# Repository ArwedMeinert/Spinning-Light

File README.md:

# Spinning Light

___  
This project combines dynamic RGB lighting with a home trainer to enhance your workout experience. The lamp pairs with a power trainer, mapping your power output to its LEDs. The displayed color corresponds to different zones based on your set FTP value. During sprints, the LEDs flash red and yellow to motivate you in your "pain cave."  

All parameters—such as LED brightness, FTP value, and the power trainer’s Bluetooth address—can be adjusted via the GUI. Under **Advanced Settings**, you can modify the zone percentages, LED filter constants, and the number of pixels.  
___  
On the main screen, sensor data for humidity and temperature is displayed. The second page shows the current power output, while the third page displays the Bluetooth address and the power trainer's name.
___
Check out the Youtube Video about the project:

---

# Microcontroller and Code

The lamp is built around an ESP32 NodeMCU Mini to keep the design compact. The firmware was developed using the Arduino IDE with the ESP32 board definitions (select Node32s). The encoder’s built-in push button is handled without an interrupt, which improves performance and reduces false button detections. A physical pull-up resistor is used, so the internal pull-up is disabled on that pin.

## Connecting Bluetooth

Bluetooth Low Energy (BTLE) is used for connectivity, with the necessary library included in the sketch. Ideally, the device writes the trainer’s address to the EEPROM for automatic reconnection on subsequent startups. However, while the ESP can reconnect automatically after a trainer is initially connected, it does not do so after a restart and must search for the trainer again. Once connected, the ESP subscribes to the power service of the trainer and receives its power data, which is then mapped to LED colors.

---

# Casing

The casing is designed for modularity. Openings for the display, encoder, temperature sensor, and USB port can be finalized after printing. This also allows you to hardcode the Bluetooth address if you prefer not to use the GUI.

---

# PCB

The PCB is designed to work with DuPont connectors for all external components. The ESP is mounted on the back to leave space for the casing lid. The ESP's USB-C port is positioned to allow external access if the plastic cover is removed. The board can be powered either via USB or through the 5V connector located in the left opening. The encoder is mounted directly on the PCB and uses three pull-up resistors—two for rotation detection and one for the push button.

Not all supports need to be screwed in; they primarily help stabilize the push button and prevent the PCB from bending under pressure.

---

# Assembly

The temperature sensor is secured to the left side of the casing. To ensure a proper fit, a section of the lid must be removed to allow the sensor's PCB to protrude. The sensor is mounted using M2 screws, fastened from the outside with a nut on the opposite side. This step should be completed first.

Next, insert the screws into the standoff holes. Use at least four screws to secure the PCB; the remaining standoffs primarily support the encoder’s push button. Once the PCB is fixed within the casing, connect the 5V supply if necessary—or use the USB port for power.

Prepare the lid by removing the sections designated for I/O components (the square for the screen and the circle for the encoder). The OLED screen should be equipped with a DuPont connector and then screwed in place. It doesn't matter whether the screen is mounted on the lid or underneath it; however, if it is mounted below, ensure it is properly supported to avoid damage.

Finally, attach the LED profile to the top, ensuring that the cable is routed into the casing. Depending on the LEDs used, prepare the cables according to the PCB's silkscreen guidelines. Once the lid is modified and the connectors are attached, carefully install the lid to avoid interfering with the sensor and encoder. Finally, secure the lid with screws, and your setup should be operational.

## Bill Of Material (BoM)

<details>
  <summary>Click to expand</summary>

| #  | Reference         | Qty | Value                 | Footprint                                                         | DNP |
|----|------------------|-----|----------------------|-----------------------------------------------------------------|-----|
| 1  | J0               | 1   | Power                | Connector_PinHeader_2.54mm:PinHeader_1x02_P2.54mm_Vertical      |     |
| 2  | J1               | 1   | Neopixel             | Connector_PinHeader_2.54mm:PinHeader_1x03_P2.54mm_Horizontal    |     |
| 3  | J2               | 1   | Temperature Sensor   | Connector_PinHeader_2.54mm:PinHeader_1x03_P2.54mm_Horizontal    |     |
| 4  | J3               | 1   | OLED                 | Connector_PinHeader_2.54mm:PinHeader_1x04_P2.54mm_Horizontal    |     |
| 5  | J4               | 1   | Reset                | Connector_PinHeader_2.54mm:PinHeader_1x02_P2.54mm_Vertical      |     |
| 6  | J5               | 1   | Reserve IO23 5VCC    | Connector_PinHeader_2.54mm:PinHeader_1x03_P2.54mm_Horizontal    |     |
| 7  | J6               | 1   | Reserve IO25 5VCC    | Connector_PinHeader_2.54mm:PinHeader_1x03_P2.54mm_Horizontal    |     |
| 8  | J7               | 1   | Reserve IO09 3V3     | Connector_PinHeader_2.54mm:PinHeader_1x03_P2.54mm_Horizontal    |     |
| 9  | J8               | 1   | Reserve IO12 3V3     | Connector_PinHeader_2.54mm:PinHeader_1x03_P2.54mm_Horizontal    |     |
| 10 | J9               | 1   | GND                  | Connector_PinHeader_2.54mm:PinHeader_1x03_P2.54mm_Horizontal    |     |
| 11 | J10              | 1   | 3V3                  | Connector_PinHeader_2.54mm:PinHeader_1x03_P2.54mm_Horizontal    |     |
| 12 | J11              | 1   | 5VCC                 | Connector_PinHeader_2.54mm:PinHeader_1x03_P2.54mm_Horizontal    |     |
| 13 | R1, R2, R3       | 3   | 10k                  | Resistor_THT:R_Axial_DIN0207_L6.3mm_D2.5mm_P7.62mm_Horizontal   |     |
| 14 | SW1              | 1   | RotaryEncoder_Switch | Rotary_Encoder:RotaryEncoder_Alps_EC11E-Switch_Vertical_H20mm   |     |
| 15 | U1               | 1   | esp32-wemos-d1-mini  | ESP32Mini:esp32-wemos-d1-mini                                   |     |
| 16 | U2               | 1   | I2C IIC BiDirektional 5V~3.3V   | Level Shifter:4xLevel Shifter                        |     |
| 17 | WS2812 Neopixel  | 1   | WS2812B LED Strip    | LED Strip (1m)                                                 |     |
| 18 | Diffusion Profile| 1   | Aluminium (1m)       | LED Diffuser Aluminum Profile                                  |     |
| 19 | DHT2302 Sensor   | 1   | DHT2302              | Temperature & Humidity Sensor                                  |     |
| 20 | OLED Display     | 1   | 0.96\" I2C OLED       | 128x64 OLED Display Module                                    |     |

</details>

### Notes:
- The profile is optional, since the controller can be used with any setup of Neopixel. When used as a standalone lamp, 1m is ideal. The amount of LEDs on the strip are also not set (standart value is 144, but it can be changed under advanced settings)
- **DHT2302**: Temperature and humidity sensor (Optional).
- **OLED display**: 0.96\" I2C screen (128x64 resolution).

---

# Usage

Upon startup, the LEDs display random colors. Pressing the encoder takes you to the menu, where you can adjust the FTP, connect the power trainer, and change the brightness (default is 50%). As you adjust the brightness, a preview gradient is shown—from the Z1 color on the first LED to the Z6 color on the last LED.

Within the menu, pressing the back button returns you to the main screen, which displays the current temperature and humidity, power output, or connected device (selectable via the encoder). A symbol in the top right corner indicates whether the power trainer is connected.

Pressing the button again returns you to the main menu. The final option in the menu is the **Advanced Settings** tab. Here, you can adjust the zone percentages (for example, changing the Z1 zone from 60% of FTP to 70% of FTP), the number of LEDs (default is 144), and the filter constants. The filter provides a gradual transition between LED colors using a low-pass algorithm. The filter constant determines the weight of the most recent power reading; for example, a constant of 0.05 means the new color is calculated as 95% of the previous color and 5% of the new value. Since the LEDs refresh multiple times per second, this results in a smooth color transition.

Similarly, the spark constant controls the number of sparks triggered when exceeding zone Z7. A higher spark constant produces more sparks during sprints, while a lower constant produces fewer sparks. The final option in the Advanced Settings tab resets the configuration data to its default values. Once you change a setting and return to the main screen, the settings are saved to the EEPROM and loaded at each startup—so you only need to configure your FTP, trainer address, brightness, and other settings once.

---

# Limitations and Improvements

- **Bluetooth Channels:**  
  ~~The lamp only works with trainers that support at least two Bluetooth channels.~~ It is only possible to connect the lamp and Zwift via bluetooth if the power trainer supports two bluetooth cahannels. It is however possible to connect Zwift via ANT+ and the lamp via BTLE (virtual shifting does not work in this case). I have tested the bluetooth connection with the Wahoo KickrCore and the Zwift Hub. Since the Wahoo KickrCore works, I suspect it will also work with other Wahoo power trainers, although I have not tested them. I welcome any additional information on this topic. See the table below.

- **Automatic Connection Issue:**  
  For some reason, upon startup the microcontroller does not automatically connect to the power trainer, even though the saved address appears to be correct. Manual connection works without issue, and the device reconnects if the power trainer loses power. Despite saving the address in the configuration data, automatic reconnection does not function as expected. I have tried scanning and multiple connection attempts at startup without success. The current workaround is to avoid powering off the lamp (as it consumes minimal power). Any advice on resolving this issue would be greatly appreciated.

- **UI Responsiveness:**  
  At times, the user interface may feel somewhat sluggish, particularly when the encoder is turned rapidly. I suspect this is primarily due to the inexpensive encoder, though other factors may contribute. Turning the encoder slowly generally results in smooth operation.

---

# Known Compatible Power Trainers with Two BT Channels

| Works           | Does Not Work     |
|-----------------|-------------------|
| Wahoo KickrCore | Zwift Hub/Hub One |

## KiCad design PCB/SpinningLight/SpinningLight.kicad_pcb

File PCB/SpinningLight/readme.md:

# PCB 
The PCB makes the wirering easier and allows for easy attatchment of additional sensors. The PCB was created using KiCAD 7.0 and this path includes all files to order and modify the files at hand. 

## Additional Modifications
The PCB already has lanes to multiple GPIO pins of the ESP, allowing easy modification and expansion with more sensor. Some inputs use the additional unused channels of the Level shifter.

___

___

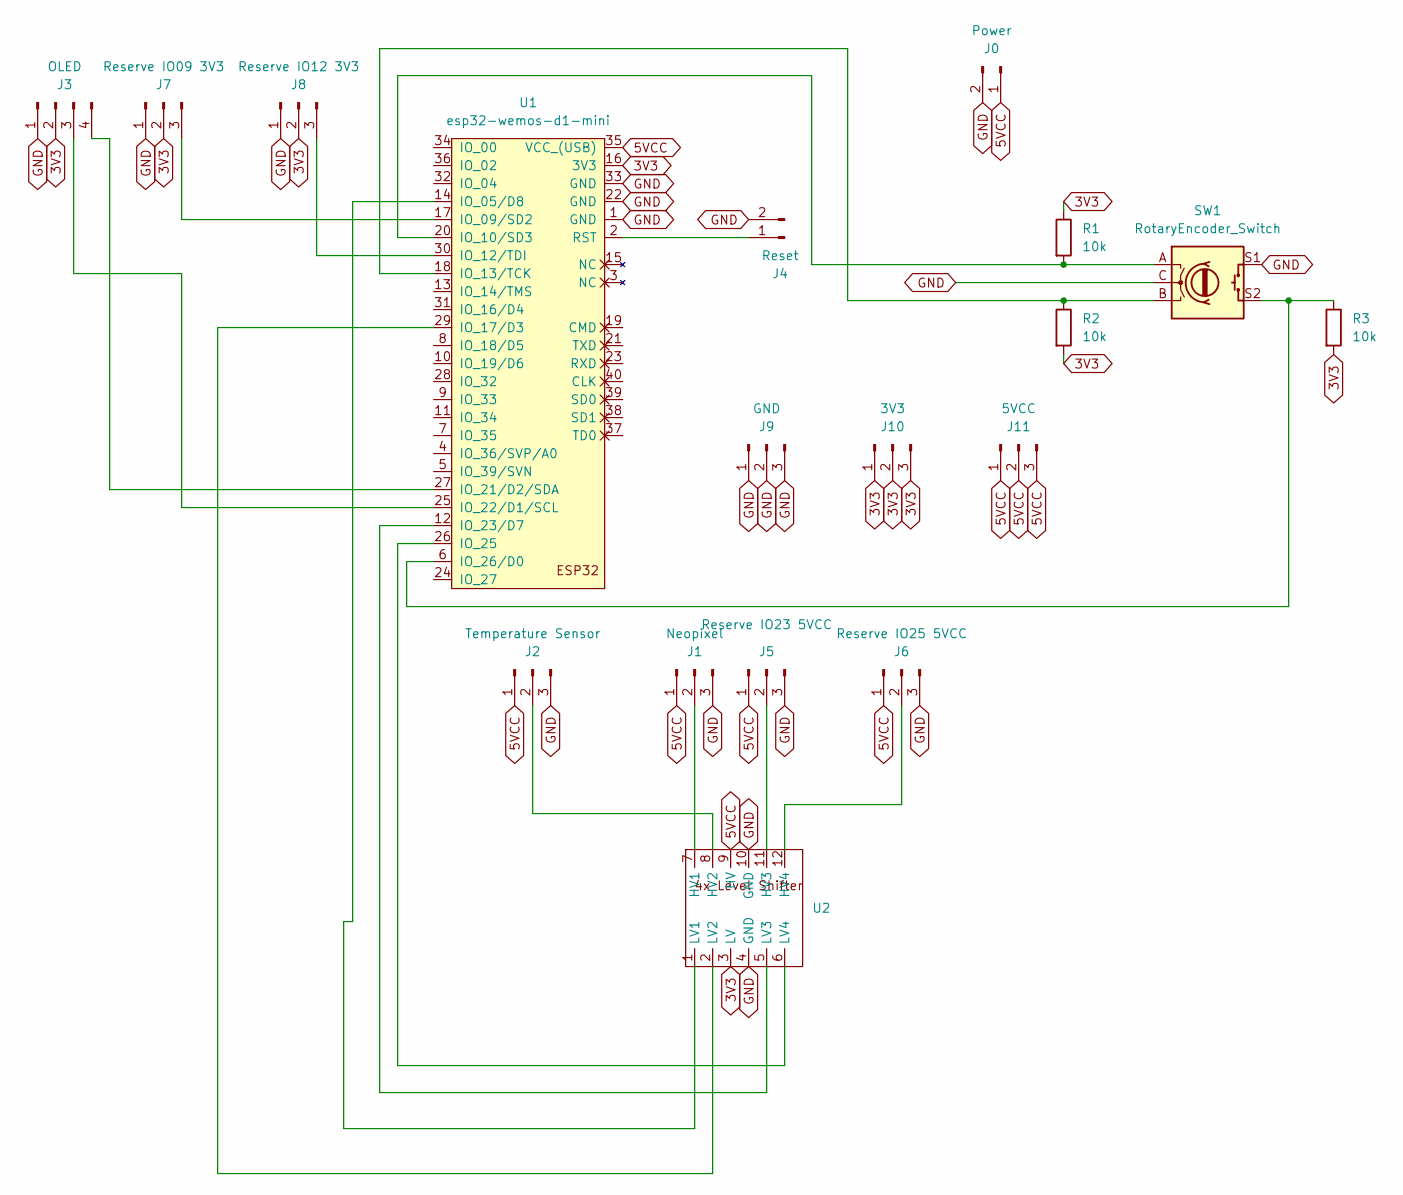
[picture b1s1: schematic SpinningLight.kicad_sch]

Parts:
J0: Power; PinHeader_1x02_P2.54mm_Vertical
J1: Neopixel; PinHeader_1x03_P2.54mm_Horizontal
J2: Temperature Sensor; PinHeader_1x03_P2.54mm_Horizontal
J3: OLED; PinHeader_1x04_P2.54mm_Horizontal
J4: Reset; PinHeader_1x02_P2.54mm_Vertical
J5: Reserve IO23 5VCC; PinHeader_1x03_P2.54mm_Horizontal
J6: Reserve IO25 5VCC; PinHeader_1x03_P2.54mm_Horizontal
J7: Reserve IO09 3V3; PinHeader_1x03_P2.54mm_Horizontal
J8: Reserve IO12 3V3; PinHeader_1x03_P2.54mm_Horizontal
J9: GND; PinHeader_1x03_P2.54mm_Horizontal
J10: 3V3; PinHeader_1x03_P2.54mm_Horizontal
J11: 5VCC; PinHeader_1x03_P2.54mm_Horizontal
R1, R2, R3: 10k; R_Axial_DIN0207_L6.3mm_D2.5mm_P7.62mm_Horizontal
SW1: RotaryEncoder_Switch; RotaryEncoder_Alps_EC11E-Switch_Vertical_H20mm
U1: esp32-wemos-d1-mini
U2: 4xLEvel Shifter

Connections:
3V3: J3.2, J7.2, J8.2, J10.1, J10.2, J10.3, R1.1, R2.2, R3.2, U1.16 (3V3), U2.3 (LV)
5VCC: J0.1, J1.1, J2.1, J5.1, J6.1, J11.1, J11.2, J11.3, U1.35 (VCC_(USB)), U2.9 (HV)
GND: J0.2, J1.3, J2.3, J3.1, J4.2, J5.3, J6.3, J7.1, J8.1, J9.1, J9.2, J9.3, SW1.C, SW1.S1, U1.1 (GND), U1.22 (GND), U1.33 (GND), U2.4 (GND), U2.10 (GND)
unnamed: J1.2, U2.7 (HV1)
unnamed: J2.2, U2.8 (HV2)
unnamed: J3.3, U1.25 (IO_22/D1/SCL)
unnamed: J3.4, U1.27 (IO_21/D2/SDA)
unnamed: J4.1, U1.2 (RST)
unnamed: J5.2, U2.11 (HV3)
unnamed: J6.2, U2.12 (HV4)
unnamed: J7.3, U1.17 (IO_09/SD2)
unnamed: J8.3, U1.30 (IO_12/TDI)
unnamed: U1.14 (IO_05/D8), U2.1 (LV1)
unnamed: R1.2, SW1.A, U1.20 (IO_10/SD3)
unnamed: R2.1, SW1.B, U1.18 (IO_13/TCK)
unnamed: U1.29 (IO_17/D3), U2.2 (LV2)
unnamed: U1.12 (IO_23/D7), U2.5 (LV3)
unnamed: U1.26 (IO_25), U2.6 (LV4)
unnamed: R3.1, SW1.S2, U1.6 (IO_26/D0)

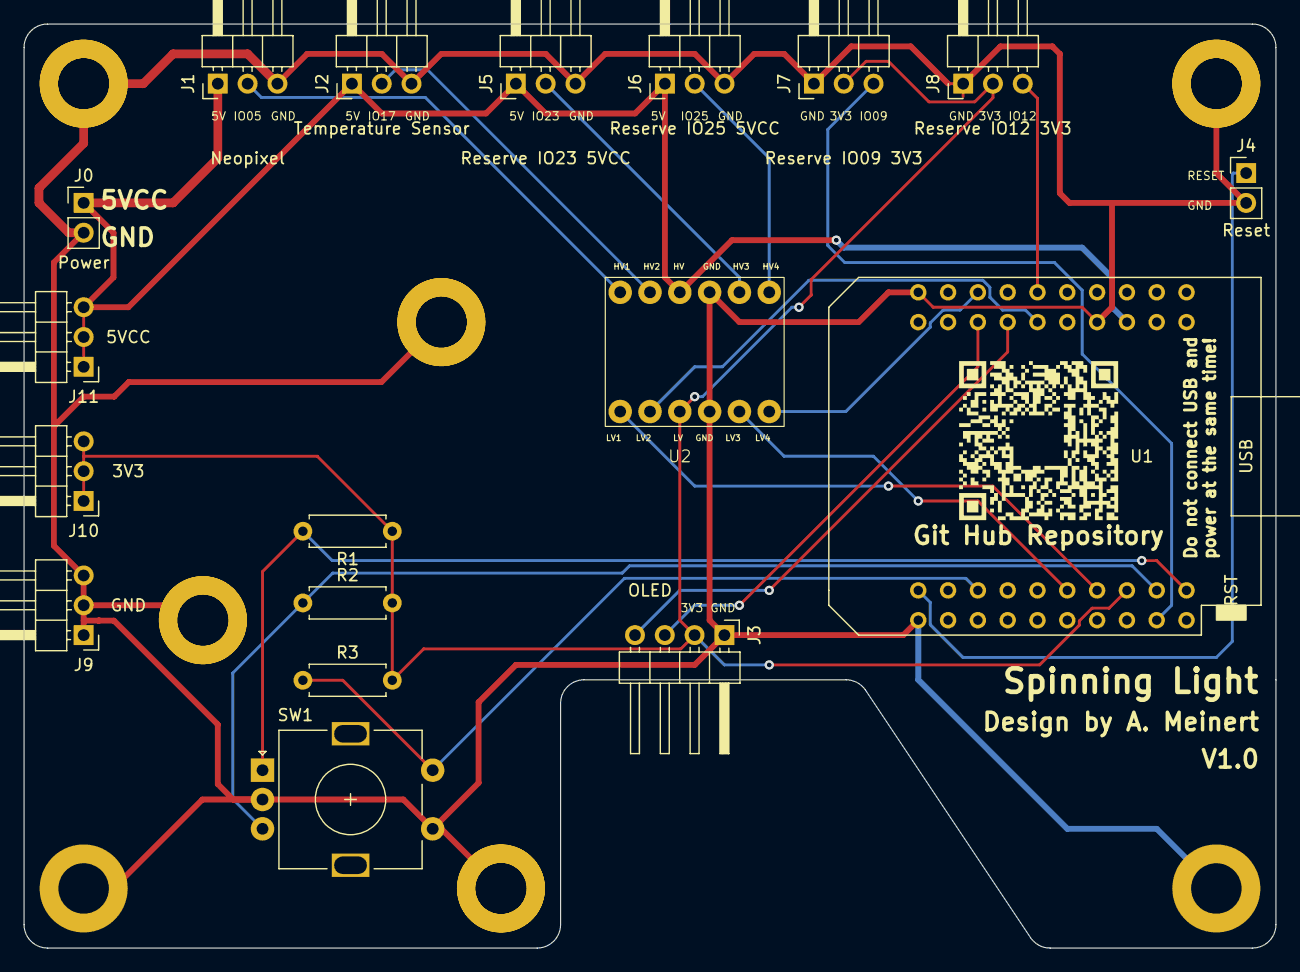
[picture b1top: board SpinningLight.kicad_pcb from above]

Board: 2 copper layers, 106.7 x 78.7 mm, 18 parts (0 on the bottom side), 19 nets.

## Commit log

2025-02-05 Added the pcb
2025-02-06 Added the casing and its assembly
2025-02-06 This time added the casing
2025-02-16 Added pictures
2025-02-16 New Code
2025-02-21 Improved startup and improved debounce
2025-03-10 Updated the STL Files for the light
2025-03-10 improved the pcb by enlarging the holes for the level shifter
    previously, the holes of the level shifter were too small making it effectively a pressfit. It has been improved here.
